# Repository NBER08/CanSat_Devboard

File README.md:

<h1 align="center">CanSat Devboard</h1>

<p align="center" width="100%">
  
</p>

***

<p align="center">
  
&nbsp; &nbsp; &nbsp; &nbsp;
  
</p>

***

## SPECIFICATIONS

| Parameter | Value | 
| --- | --- |
| Dimensions | 64.06 × 43.56 mm |

***

## DIRECTORY STRUCTURE

    .
    ├─ Computations       # Misc calculations
    ├─ HTML               # HTML files for generated webpage
    ├─ Images             # Pictures and renders
    │
    ├─ kibot_resources    # External resources for KiBot
    │  ├─ colors          # Color theme for KiCad
    │  ├─ fonts           # Fonts used in the project
    │  ├─ scripts         # External scripts used with KiBot
    │  └─ templates       # Templates for KiBot generated reports
    │
    ├─ kibot_yaml         # KiBot YAML config files
    ├─ KiRI               # KiRI (PCB diff viewer) files
    │
    ├─ lib                # KiCad footprint and symbol libraries
    │  ├─ 3d_models       # Component 3D models
    │  ├─ lib_fp          # Footprint libraries
    │  └─ lib_sym         # Symbol libraries
    │
    ├─ Logos              # Logos
    │
    ├─ Manufacturing      # Assembly and fabrication documents
    │  ├─ Assembly        # Assembly documents (BoM, pos, notes)
    │  │
    │  └─ Fabrication     # Fabrication documents (ZIP, notes)
    │     ├─ Drill Tables # CSV drill tables
    │     └─ Gerbers      # Gerbers
    │
    ├─ Report             # Reports for ERC/DRC
    ├─ Schematic          # PDF of schematic
    ├─ Templates          # Title block templates
    ├─ Testing
    │  └─ Testpoints      # Testpoints tables      
    │
    └─ Variants           # Outputs for assembly variants

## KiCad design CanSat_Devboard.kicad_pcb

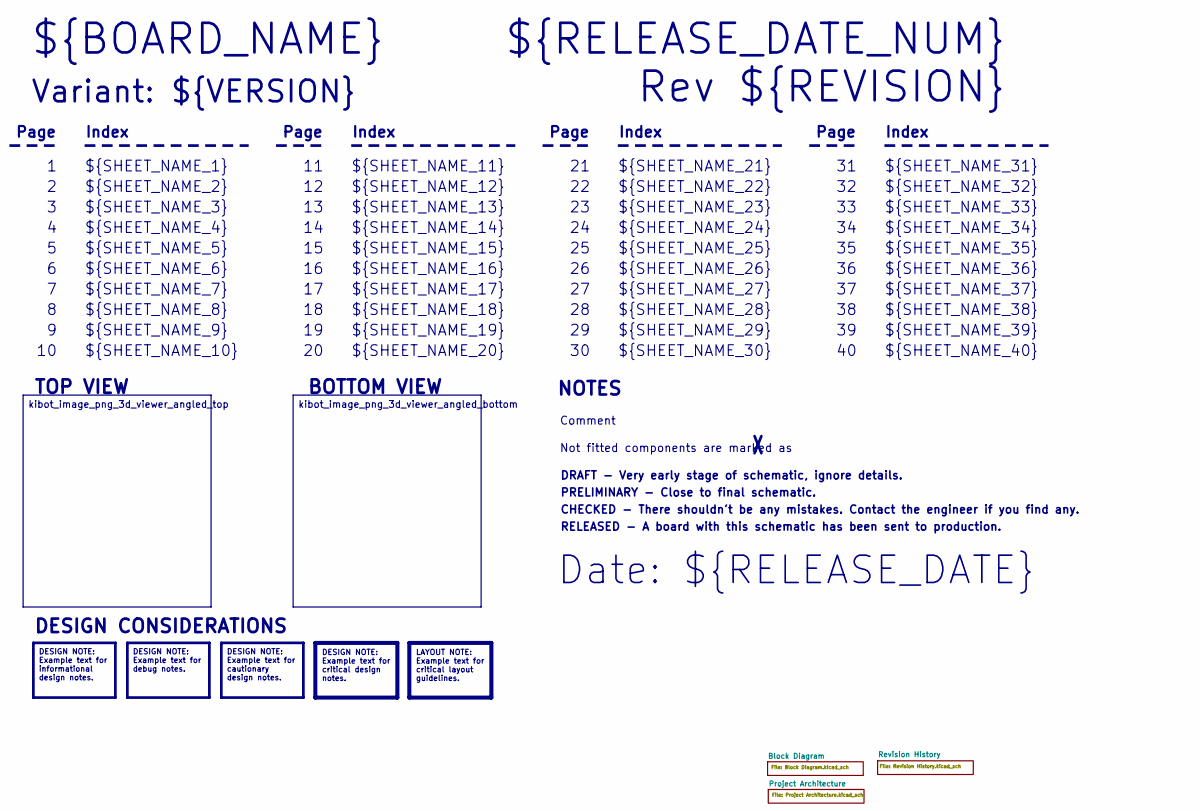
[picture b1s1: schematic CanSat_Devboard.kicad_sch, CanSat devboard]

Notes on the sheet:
Variant: ${VERSION}
RELEASED - A board with this schematic has been sent to production.
${SHEET_NAME_24}
Index
Page
PRELIMINARY - Close to final schematic.
${SHEET_NAME_22}
DRAFT - Very early stage of schematic, ignore details.
${SHEET_NAME_12}
${SHEET_NAME_8}
${SHEET_NAME_2}
${SHEET_NAME_5}
${SHEET_NAME_20}
${SHEET_NAME_23}
${RELEASE_DATE_NUM}
${SHEET_NAME_35}
Not fitted components are marked as
${SHEET_NAME_11}
${SHEET_NAME_6}
${SHEET_NAME_37}
${SHEET_NAME_26}
${SHEET_NAME_36}
Rev ${REVISION}
${SHEET_NAME_15}
CHECKED - There shouldn't be any mistakes. Contact the engineer if you find any.
BOTTOM VIEW
${SHEET_NAME_14}
${SHEET_NAME_21}
${SHEET_NAME_17}
${SHEET_NAME_18}
Date: ${RELEASE_DATE}
${SHEET_NAME_7}
${SHEET_NAME_31}
${BOARD_NAME}
NOTES
${SHEET_NAME_40}
${SHEET_NAME_39}
${SHEET_NAME_32}
${SHEET_NAME_1}
${SHEET_NAME_9}

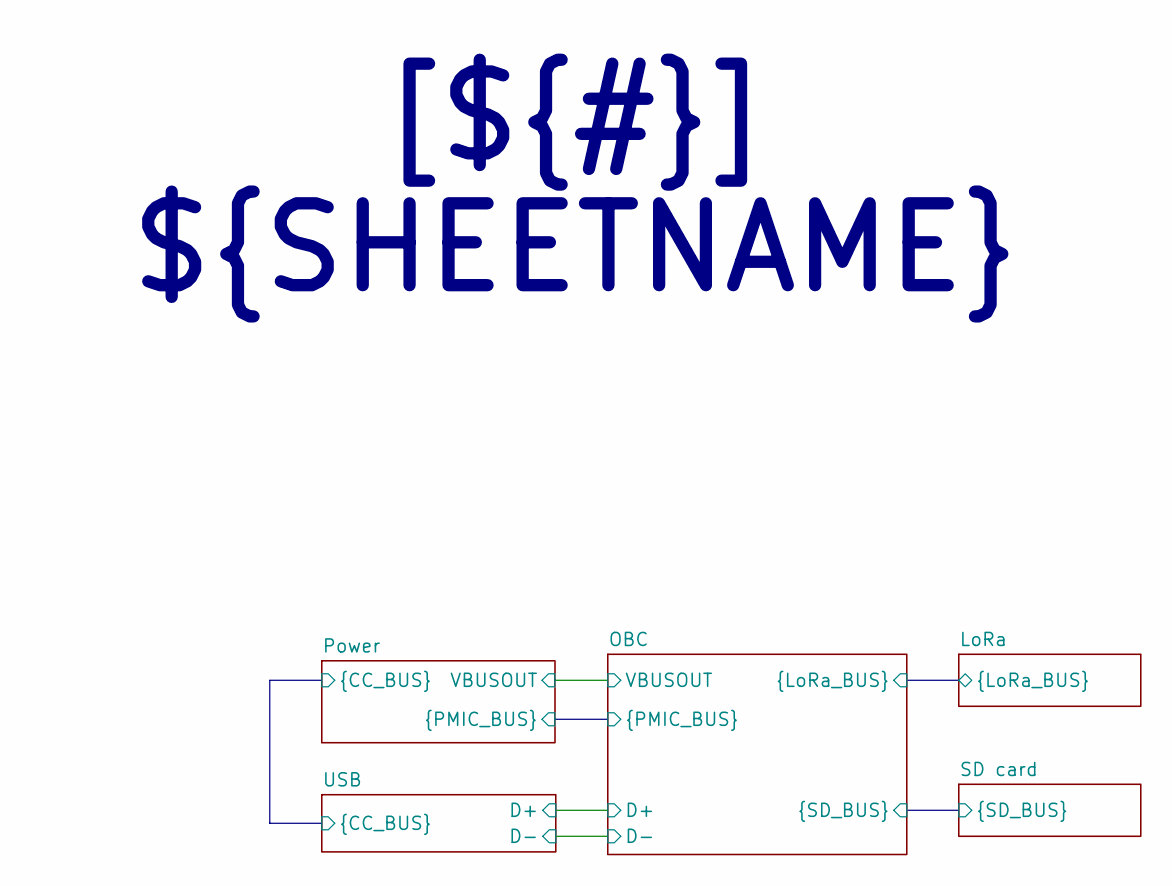
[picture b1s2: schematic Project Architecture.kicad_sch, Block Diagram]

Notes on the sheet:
[${#}] ${SHEETNAME}

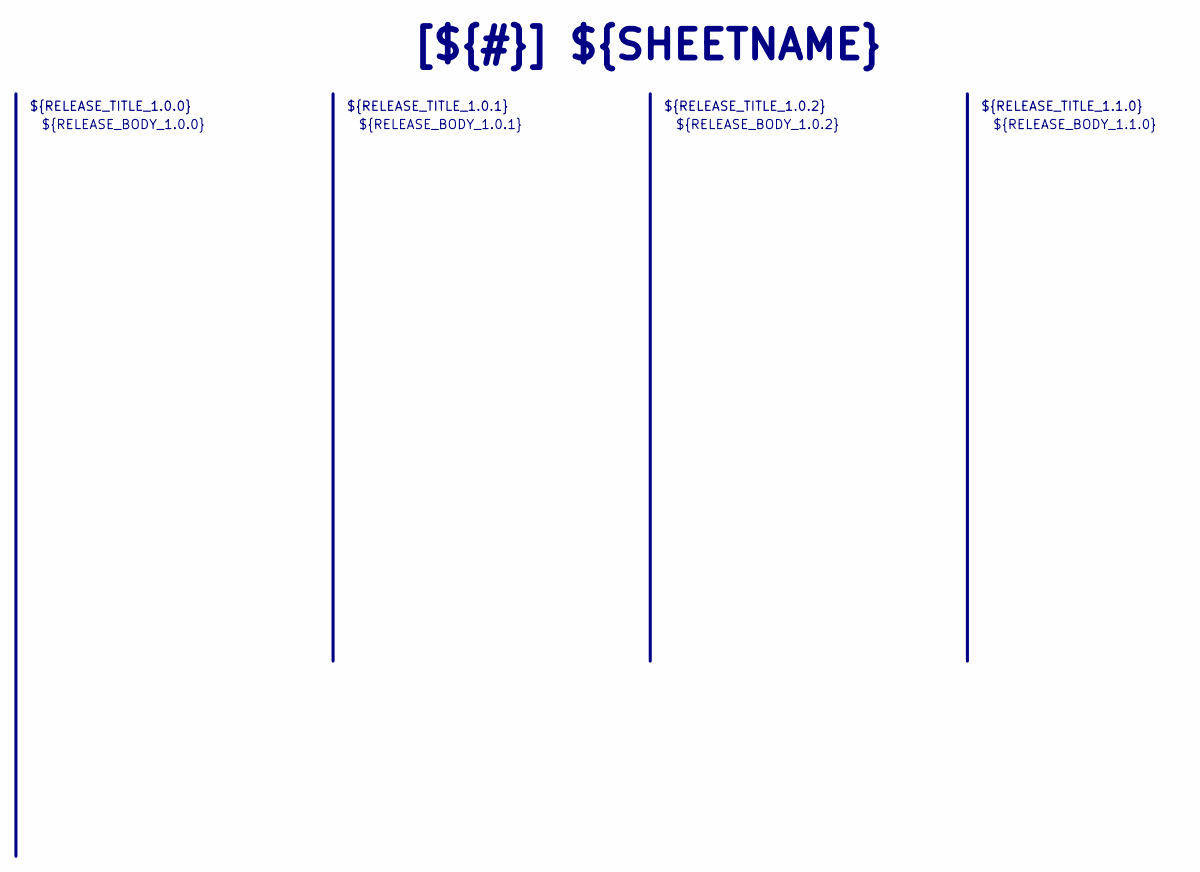
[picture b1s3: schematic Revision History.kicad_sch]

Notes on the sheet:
${RELEASE_BODY_1.0.1}
[${#}] ${SHEETNAME}
${RELEASE_BODY_1.0.2}
${RELEASE_TITLE_1.0.0}
${RELEASE_TITLE_1.0.1}
${RELEASE_BODY_1.0.0}
${RELEASE_BODY_1.1.0}
${RELEASE_TITLE_1.1.0}
${RELEASE_TITLE_1.0.2}

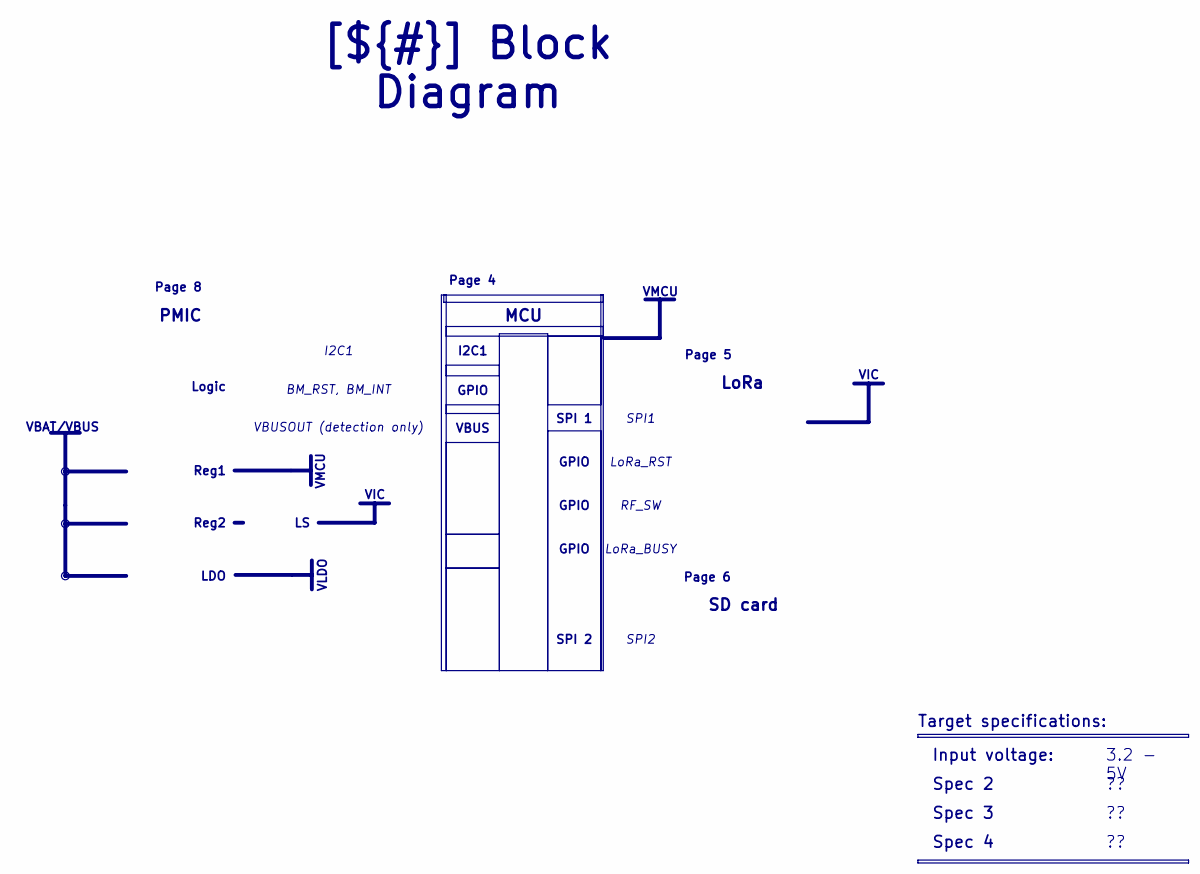
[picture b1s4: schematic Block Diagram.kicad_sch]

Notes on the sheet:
VIC
VBAT/VBUS
VMCU
VLDO
LoRa
Spec 4
Reg1
Reg2
3.2 - 5V
VBUSOUT (detection only)
MCU
GPIO
SPI1
Page 8
SPI2
SPI 2
SD card
LoRa_BUSY
I2C1
RF_SW
[${#}] ${TITLE}
Input voltage:
PMIC
Page 6
Target specifications:
VBUS
LDO
SPI 1
BM_RST, BM_INT
Spec 3
Spec 2
LoRa_RST
Logic
Page 4
Page 5

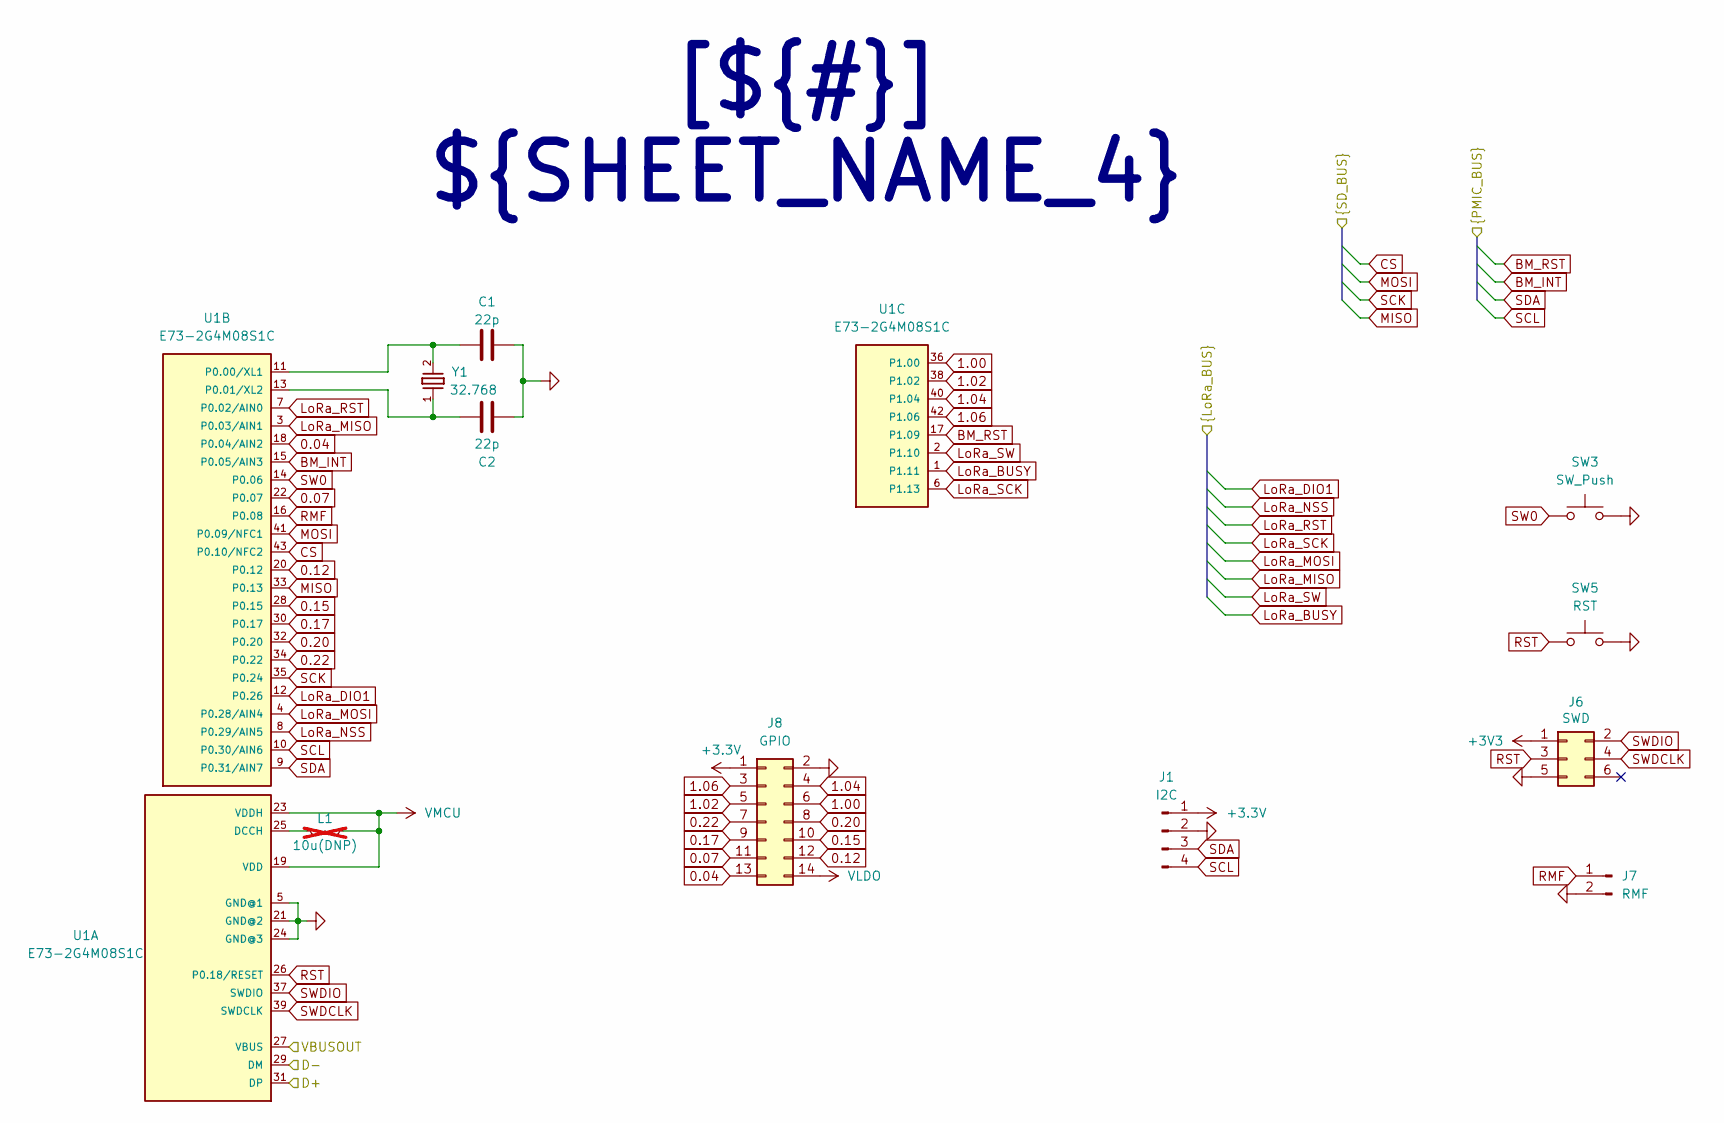
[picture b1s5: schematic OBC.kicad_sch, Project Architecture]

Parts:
C1, C2: 22p; C_0603_1608Metric
J1: I2C; PinHeader_1x04_P2.54mm_Vertical
J6: SWD; PinHeader_2x03_P2.54mm_Vertical
J7: RMF; PinHeader_1x02_P2.54mm_Vertical
J8: GPIO; PinHeader_2x07_P2.54mm_Vertical
L1: 10u(DNP); L_1210_3225Metric; not fitted
SW3: SW_Push; SW_Push_1P1T_NO_CK_KMR2
SW5: RST; SW_Push_1P1T_NO_CK_KMR2
U1: E73-2G4M08S1C
Y1: 32.768; WE-XTAL_CFPX-217

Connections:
0.04: J8.13, U1.18 (P0.04/AIN2)
0.07: J8.11, U1.22 (P0.07)
0.12: J8.12, U1.20 (P0.12)
0.15: J8.10, U1.28 (P0.15)
0.17: J8.9, U1.30 (P0.17)
0.20: J8.8, U1.32 (P0.20)
0.22: J8.7, U1.34 (P0.22)
1.00: J8.6, U1.36 (P1.00)
1.02: J8.5, U1.38 (P1.02)
1.04: J8.4, U1.40 (P1.04)
1.06: J8.3, U1.42 (P1.06)
+3.3V: J1.1, J8.1; also elsewhere on the board
+3V3: J6.1
/Project Architecture/OBC/D+: U1.31 (DP); also elsewhere on the board
/Project Architecture/OBC/D-: U1.29 (DM); also elsewhere on the board
BM_INT: U1.15 (P0.05/AIN3); also elsewhere on the board
BM_RST: U1.17 (P1.09); also elsewhere on the board
CS: U1.43 (P0.10/NFC2); also elsewhere on the board
GND: C1.1, C2.1, J1.2, J6.5, J7.2, J8.2, SW3.2, SW5.2, U1.5 (GND@1), U1.21 (GND@2), U1.24 (GND@3); also elsewhere on the board
LoRa_BUSY: U1.1 (P1.11); also elsewhere on the board
LoRa_DIO1: U1.12 (P0.26); also elsewhere on the board
LoRa_MISO: U1.3 (P0.03/AIN1); also elsewhere on the board
LoRa_MOSI: U1.4 (P0.28/AIN4); also elsewhere on the board
LoRa_NSS: U1.8 (P0.29/AIN5); also elsewhere on the board
LoRa_RST: U1.7 (P0.02/AIN0); also elsewhere on the board
LoRa_SCK: U1.6 (P1.13); also elsewhere on the board
LoRa_SW: U1.2 (P1.10); also elsewhere on the board
MISO: U1.33 (P0.13); also elsewhere on the board
MOSI: U1.41 (P0.09/NFC1); also elsewhere on the board
unnamed: L1.1, U1.25 (DCCH)
unnamed: C1.2, U1.11 (P0.00/XL1), Y1.2
unnamed: C2.2, U1.13 (P0.01/XL2), Y1.1
RMF: J7.1, U1.16 (P0.08)
RST: J6.3, SW5.1, U1.26 (P0.18/RESET)
SCK: U1.35 (P0.24); also elsewhere on the board
SCL: J1.4, U1.10 (P0.30/AIN6); also elsewhere on the board
SDA: J1.3, U1.9 (P0.31/AIN7); also elsewhere on the board
SW0: SW3.1, U1.14 (P0.06)
SWDCLK: J6.4, U1.39 (SWDCLK)
SWDIO: J6.2, U1.37 (SWDIO)
VBUSOUT: U1.27 (VBUS); also elsewhere on the board
VLDO: J8.14; also elsewhere on the board
VMCU: L1.2, U1.19 (VDD), U1.23 (VDDH); also elsewhere on the board

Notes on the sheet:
[${#}] ${SHEET_NAME_4}

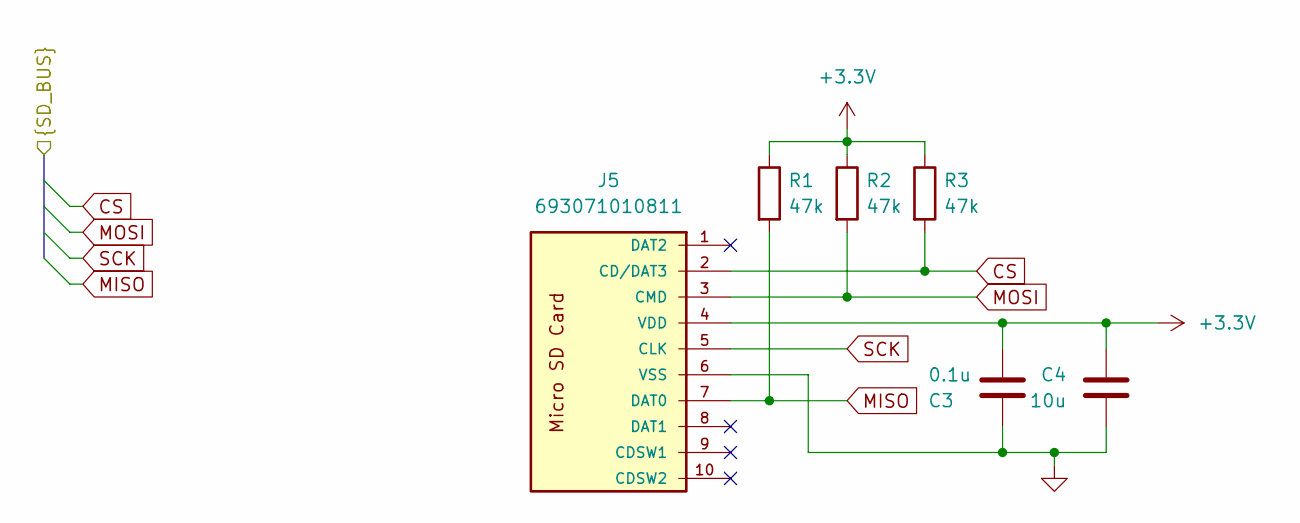
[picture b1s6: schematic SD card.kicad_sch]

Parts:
C3: 0.1u; C_0603_1608Metric
C4: 10u; C_0603_1608Metric
J5: 693071010811
R1, R2, R3: 47k; R_0603_1608Metric

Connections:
+3.3V: C3.2, C4.2, J5.4 (VDD), R1.1, R2.1, R3.1; also elsewhere on the board
CS: J5.2 (CD/DAT3), R3.2; also elsewhere on the board
GND: C3.1, C4.1, J5.6 (VSS); also elsewhere on the board
MISO: J5.7 (DAT0), R1.2; also elsewhere on the board
MOSI: J5.3 (CMD), R2.2; also elsewhere on the board
SCK: J5.5 (CLK); also elsewhere on the board

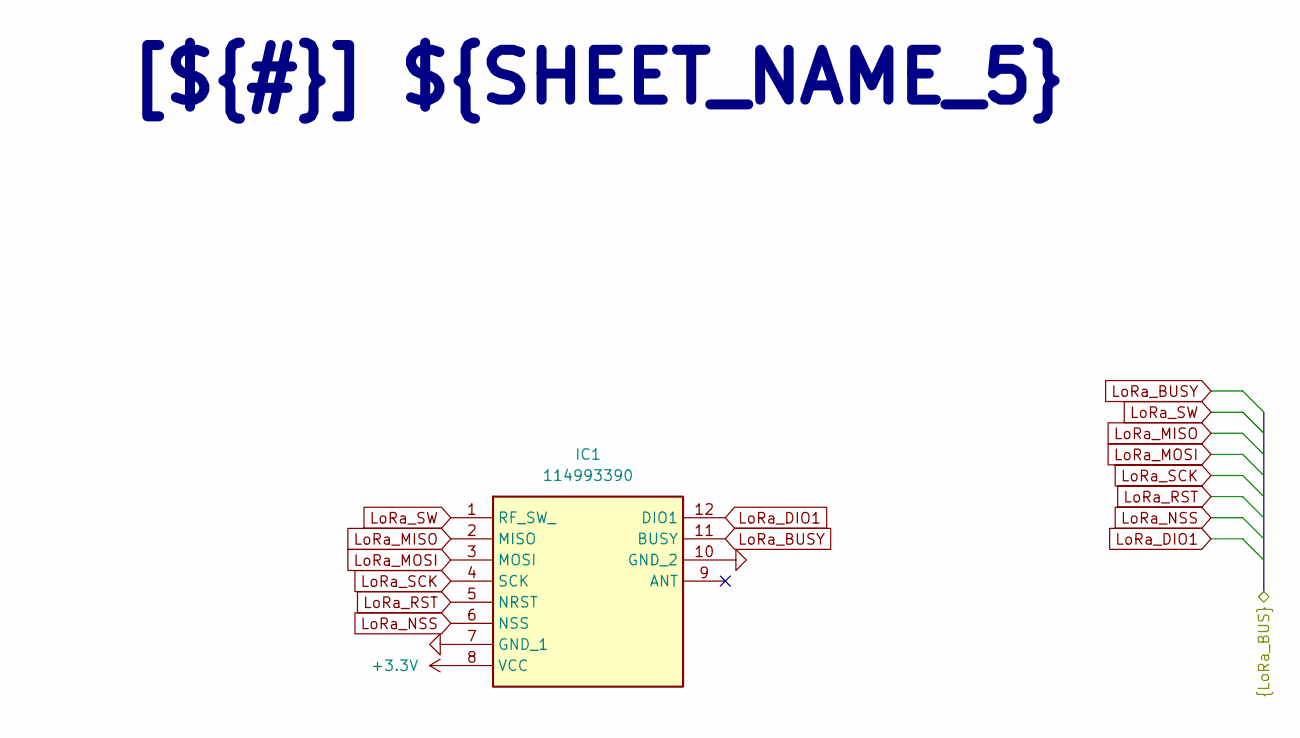
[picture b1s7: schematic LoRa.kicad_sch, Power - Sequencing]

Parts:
IC1: 114993390; Mouser Part Number 713-114993390

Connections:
+3.3V: IC1.8 (VCC); also elsewhere on the board
GND: IC1.7 (GND_1), IC1.10 (GND_2); also elsewhere on the board
LoRa_BUSY: IC1.11 (BUSY); also elsewhere on the board
LoRa_DIO1: IC1.12 (DIO1); also elsewhere on the board
LoRa_MISO: IC1.2 (MISO); also elsewhere on the board
LoRa_MOSI: IC1.3 (MOSI); also elsewhere on the board
LoRa_NSS: IC1.6 (NSS); also elsewhere on the board
LoRa_RST: IC1.5 (NRST); also elsewhere on the board
LoRa_SCK: IC1.4 (SCK); also elsewhere on the board
LoRa_SW: IC1.1 (RF_SW_); also elsewhere on the board

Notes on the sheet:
[${#}] ${SHEET_NAME_5}

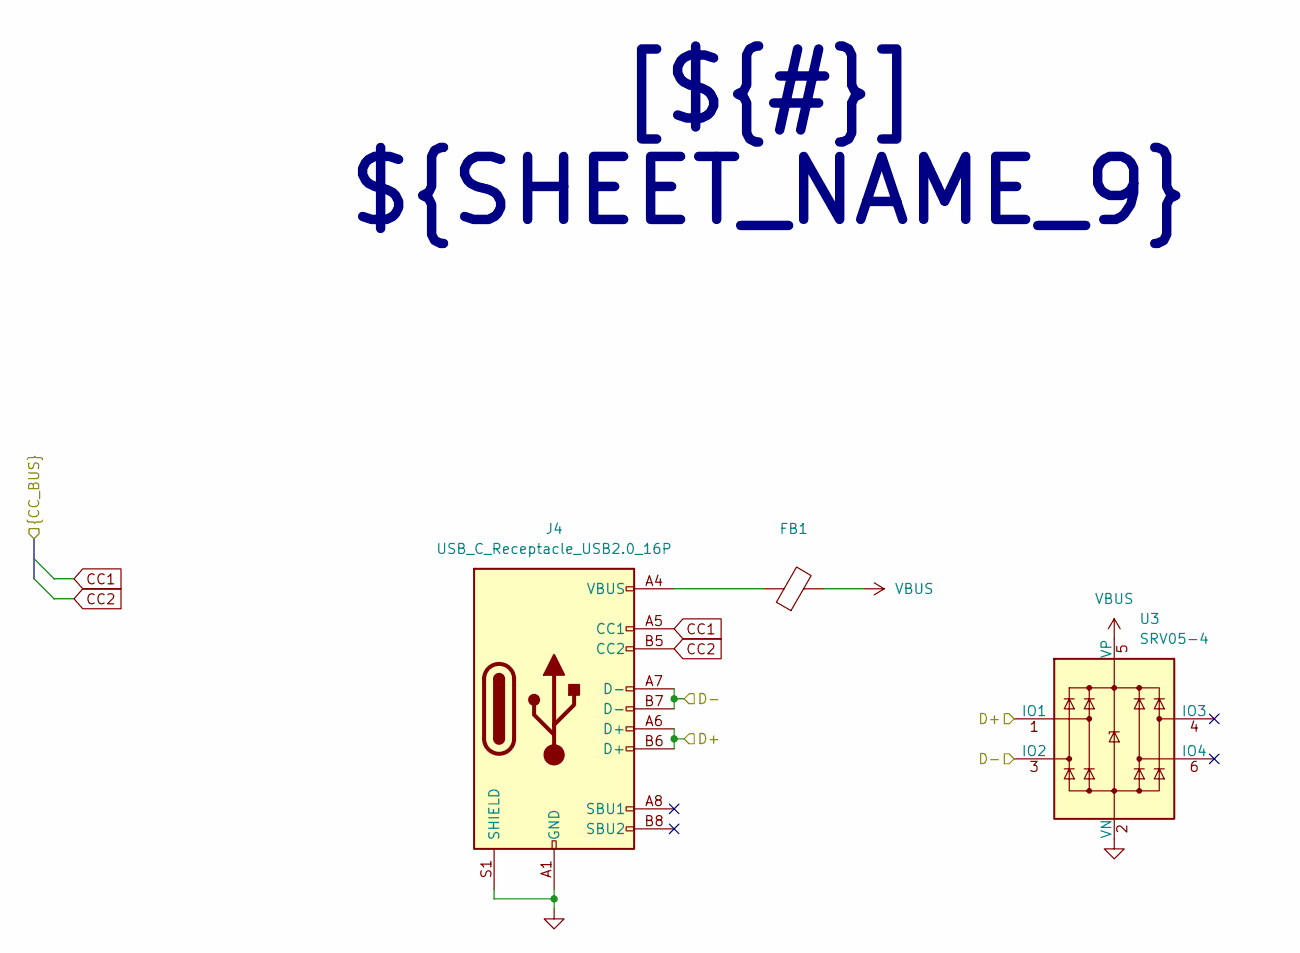
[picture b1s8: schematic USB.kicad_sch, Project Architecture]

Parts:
FB1: LI0603G121R-10; L_0603_1608Metric
J4: USB_C_Receptacle_USB2.0_16P; USB_C_Receptacle_GCT_USB4105-xx-A_16P_TopMnt_Horizontal
U3: SRV05-4; SOT-23-6_Handsoldering

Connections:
/Project Architecture/OBC/D+: J4.A6 (D+), J4.B6 (D+), U3.1 (IO1); also elsewhere on the board
/Project Architecture/OBC/D-: J4.A7 (D-), J4.B7 (D-), U3.3 (IO2); also elsewhere on the board
CC1: J4.A5 (CC1); also elsewhere on the board
CC2: J4.B5 (CC2); also elsewhere on the board
GND: J4.A1 (GND), J4.A12 (GND), J4.B1 (GND), J4.B12 (GND), J4.S1 (SHIELD), U3.2 (VN); also elsewhere on the board
unnamed: FB1.1, J4.A4 (VBUS), J4.A9 (VBUS), J4.B4 (VBUS), J4.B9 (VBUS)
VBUS: FB1.2, U3.5 (VP); also elsewhere on the board

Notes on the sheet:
[${#}] ${SHEET_NAME_9}

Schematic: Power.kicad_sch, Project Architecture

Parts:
C11, C12: 1u; C_0603_1608Metric
C13: 2u2; C_0603_1608Metric
C14, C16, C17, C18, C19: 10u; C_0603_1608Metric
C15: 0.1u; C_0603_1608Metric
D4: Amber; LED_0603_1608Metric
D5: Green; LED_0603_1608Metric
D6: Blue; LED_0603_1608Metric
J3: Conn_01x03_Pin; JST_XH_B3B-XH-A_1x03_P2.50mm_Vertical
L4, L5: 2u2; L_1812_4532Metric
R11, R12: 4k7; R_0603_1608Metric
R13: 310; R_0603_1608Metric
R14, R15: 180; R_0603_1608Metric
R16: 500k; R_0603_1608Metric
R17: 47k; R_0603_1608Metric
SW4: SHPHLD; SW_Push_1P1T_NO_CK_KMR2
TP7: VMCU; TestPoint_Pad_D1.0mm
TP8: VSYS; TestPoint_Pad_D1.0mm
TP9: 3V3; TestPoint_Pad_D1.0mm
TP10: VLDO; TestPoint_Pad_D1.0mm
U4: NPM1300-QEAA-R7; QFN32_5X5_NOR

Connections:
+3.3V: C16.2, L5.2, TP9.1 (1_1), U4.1 (VOUT1); also elsewhere on the board
BM_INT: U4.8 (GPIO1); also elsewhere on the board
BM_RST: U4.7 (GPIO0); also elsewhere on the board
CC1: U4.23 (CC1); also elsewhere on the board
CC2: U4.24 (CC2); also elsewhere on the board
GND: C11.1, C12.1, C13.1, C14.2, C15.2, C16.1, C17.1, C18.1, C19.1, J3.2, R16.2, R17.2, SW4.2, U4.2 (PVSS1), U4.6 (PVSS2), U4.33 (AVSS); also elsewhere on the board
NTC: J3.1, U4.18 (NTC)
unnamed: D4.2 (A), R13.1
unnamed: D4.1 (K), U4.25 (LED0)
unnamed: D5.2 (A), R14.1
unnamed: D5.1 (K), U4.26 (LED1)
unnamed: D6.2 (A), R15.1
unnamed: D6.1 (K), U4.27 (LED2)
unnamed: SW4.1, U4.15 (SHPHLD)
unnamed: R17.1, U4.17 (VSET1)
unnamed: R16.1, U4.16 (VSET2)
SCL: R11.2, U4.14 (SCL); also elsewhere on the board
SDA: R12.1, U4.13 (SDA); also elsewhere on the board
SW1: L5.1, U4.3 (SW1)
SW2: L4.2, U4.5 (SW2)
VBAT: C13.2, J3.3, U4.19 (VBAT)
VBUS: C12.2, U4.21 (VBUS); also elsewhere on the board
VBUSOUT: C11.2, U4.22 (VBUSOUT); also elsewhere on the board
VLDO: TP10.1 (1_1), U4.29 (LSOUT1/VOUTLDO1); also elsewhere on the board
VMCU: C14.1, C15.1, L4.1, R11.1, R12.2, TP7.1 (1_1), U4.12 (VDDIO), U4.32 (VOUT2); also elsewhere on the board
VSYS: C17.2, C18.2, C19.2, R13.2, R14.2, R15.2, TP8.1 (1_1), U4.4 (PVDD), U4.20 (VSYS), U4.28 (LSIN1/VINLDO1)

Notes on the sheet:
LDO mode
47k -> 1.8V 500k -> 2.7V
Load switch mode
[${#}] ${SHEET_NAME_8}

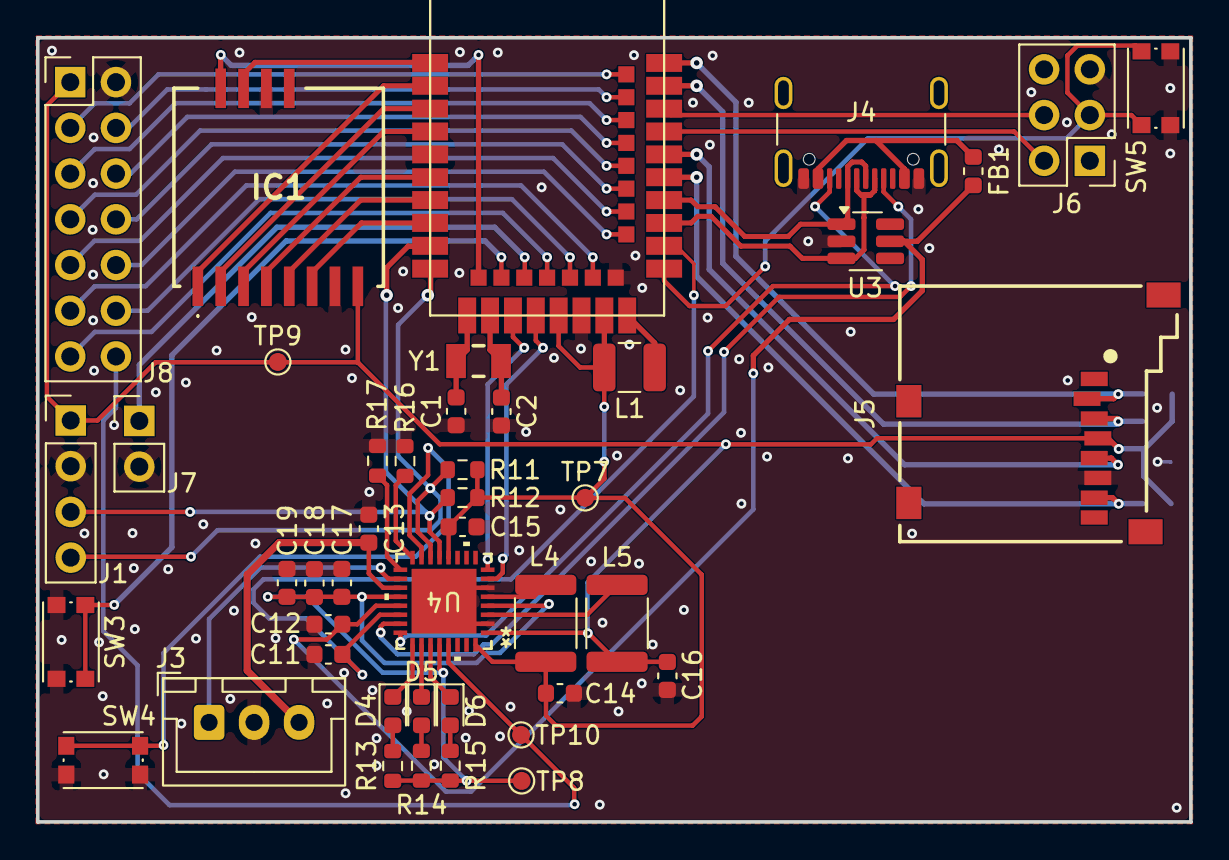
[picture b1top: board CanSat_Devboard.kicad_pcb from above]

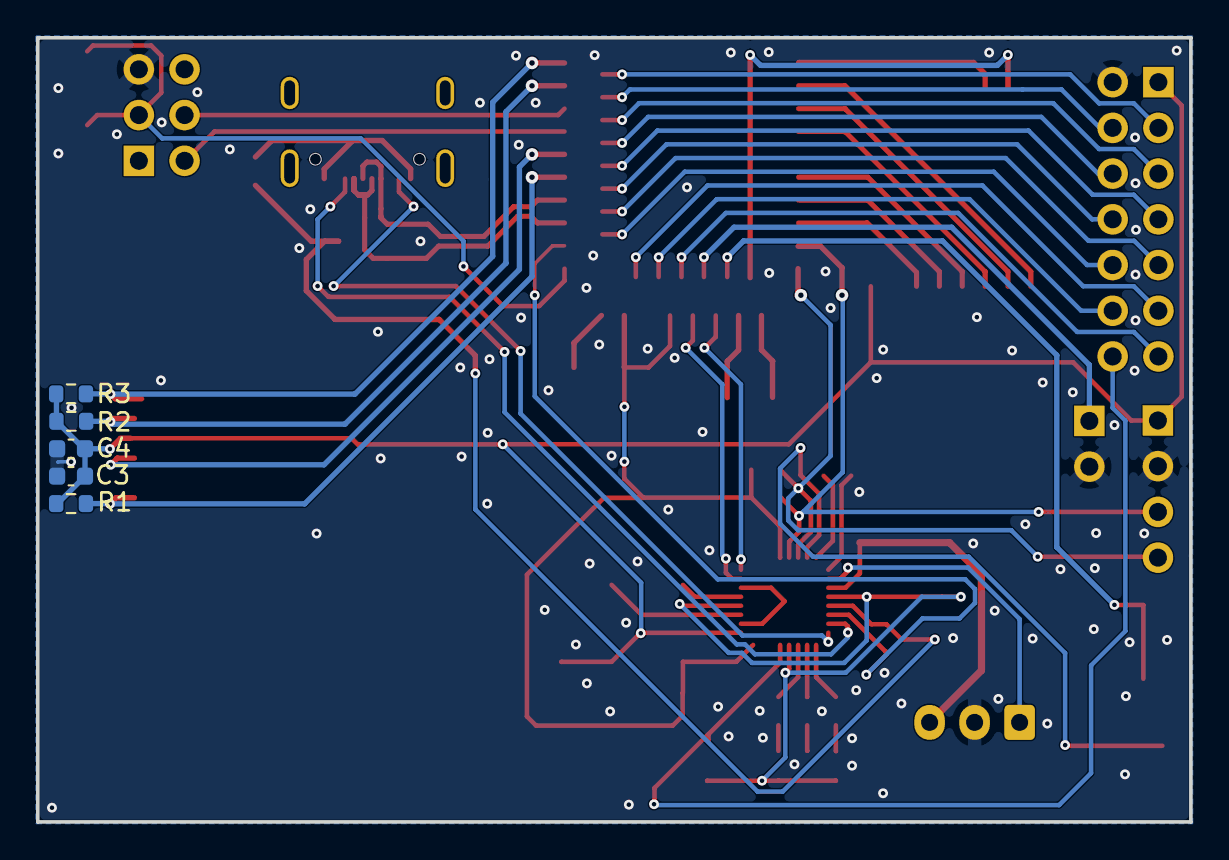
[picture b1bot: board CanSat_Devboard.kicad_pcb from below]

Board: 4 copper layers, 64.1 x 43.6 mm, 49 parts (5 on the bottom side), 60 nets.

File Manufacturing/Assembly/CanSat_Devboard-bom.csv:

Row,Quantity Per PCB,References,Value,Datasheet,Footprint,Description,Manufacturer,Manufacturer Part Number,Supplier Part Number
1,2,C1 C2,22p,,C_0603_1608Metric,Unpolarized capacitor,,,
2,2,C3 C15,0.1u,,C_0603_1608Metric,Unpolarized capacitor,,,
3,2,C11 C12,1u,,C_0603_1608Metric,Unpolarized capacitor,,,
4,3,C13 L4 L5,2u2,,C_0603_1608Metric,"Unpolarized capacitor Inductor, small symbol",,,
5,6,C4 C14 C16 C17 C18 C19,10u,,C_0603_1608Metric,Unpolarized capacitor,,,
6,1,D4,Amber,,LED_0603_1608Metric,"Light emitting diode, small symbol",,,
7,1,D6,Blue,,LED_0603_1608Metric,"Light emitting diode, small symbol",,,
8,1,D5,Green,,LED_0603_1608Metric,"Light emitting diode, small symbol",,,
9,1,FB1,LI0603G121R-10,,L_0603_1608Metric,Ferrite bead,,,
10,1,IC1,114993390,,114993390,"RF Modules Wio-SX1262 Wireless Module (Bulk), SX1262 embedded, supports LoRa&LoRaWAN on EU868 & US915",,,
11,1,J5,693071010811,,693071010811,"693 Series, Header for use with Micro SD Card | Wurth Electronics 693071010811",,,
12,6,J1 J3 J4 J6 J7 J8,I2C,,PinHeader_1x04_P2.54mm_Vertical,"Generic connector, single row, 01x04, script generated Generic connector, single row, 01x03, script generated USB 2.0-only 16P Type-C Receptacle connector Generic connector, single row, 01x02, script generated Generic connector, double row, 02x07, odd/even pin numbering scheme (row 1 odd numbers, row 2 even numbers), script generated (kicad-library-utils/schlib/autogen/connector/)",,,
13,2,R14 R15,180,,R_0603_1608Metric,"Resistor, small symbol",,,
14,1,R13,310,,R_0603_1608Metric,"Resistor, small symbol",,,
15,2,R11 R12,4k7,,R_0603_1608Metric,Resistor,,,
16,4,R1 R2 R3 R17,47k,,R_0603_1608Metric,Resistor,,,
17,1,R16,150k,,R_0603_1608Metric,Resistor,,,
18,1,SW5,RST,,SW_Push_1P1T_NO_CK_KMR2,"Push button switch, generic, two pins",,,
19,1,SW4,SHPHLD,,SW_Push_1P1T_NO_CK_KMR2,"Push button switch, generic, two pins",,,
20,1,SW3,SW_Push,,SW_Push_1P1T_NO_CK_KMR2,"Push button switch, generic, two pins",,,
21,1,U1,E73-2G4M08S1C,,E73-2G4M08S1C,nRF52840 2.4GHZ SMD Wireless Module,,,
22,1,U4,NPM1300-QEAA-R7,https://docs.nordicsemi.com/viewer/book-attachment/kL6EnWEP1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,QFN32_5X5_NOR,,,,
23,1,U3,SRV05-4,http://www.onsemi.com/pub/Collateral/SRV05-4-D.PDF,SOT-23-6_Handsoldering,"ESD Protection Diodes with Low Clamping Voltage, SOT-23-6",,,
24,1,Y1,32.768,,WE-XTAL_CFPX-217,"32.768 kHz ±20ppm Crystal 12.5pF 70 kOhms 2-SMD, No Lead",,,

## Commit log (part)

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2026-06-22 added workflow YAML
